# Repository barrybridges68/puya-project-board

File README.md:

# puya-project-board
Multi purpose PUYA py32 project board

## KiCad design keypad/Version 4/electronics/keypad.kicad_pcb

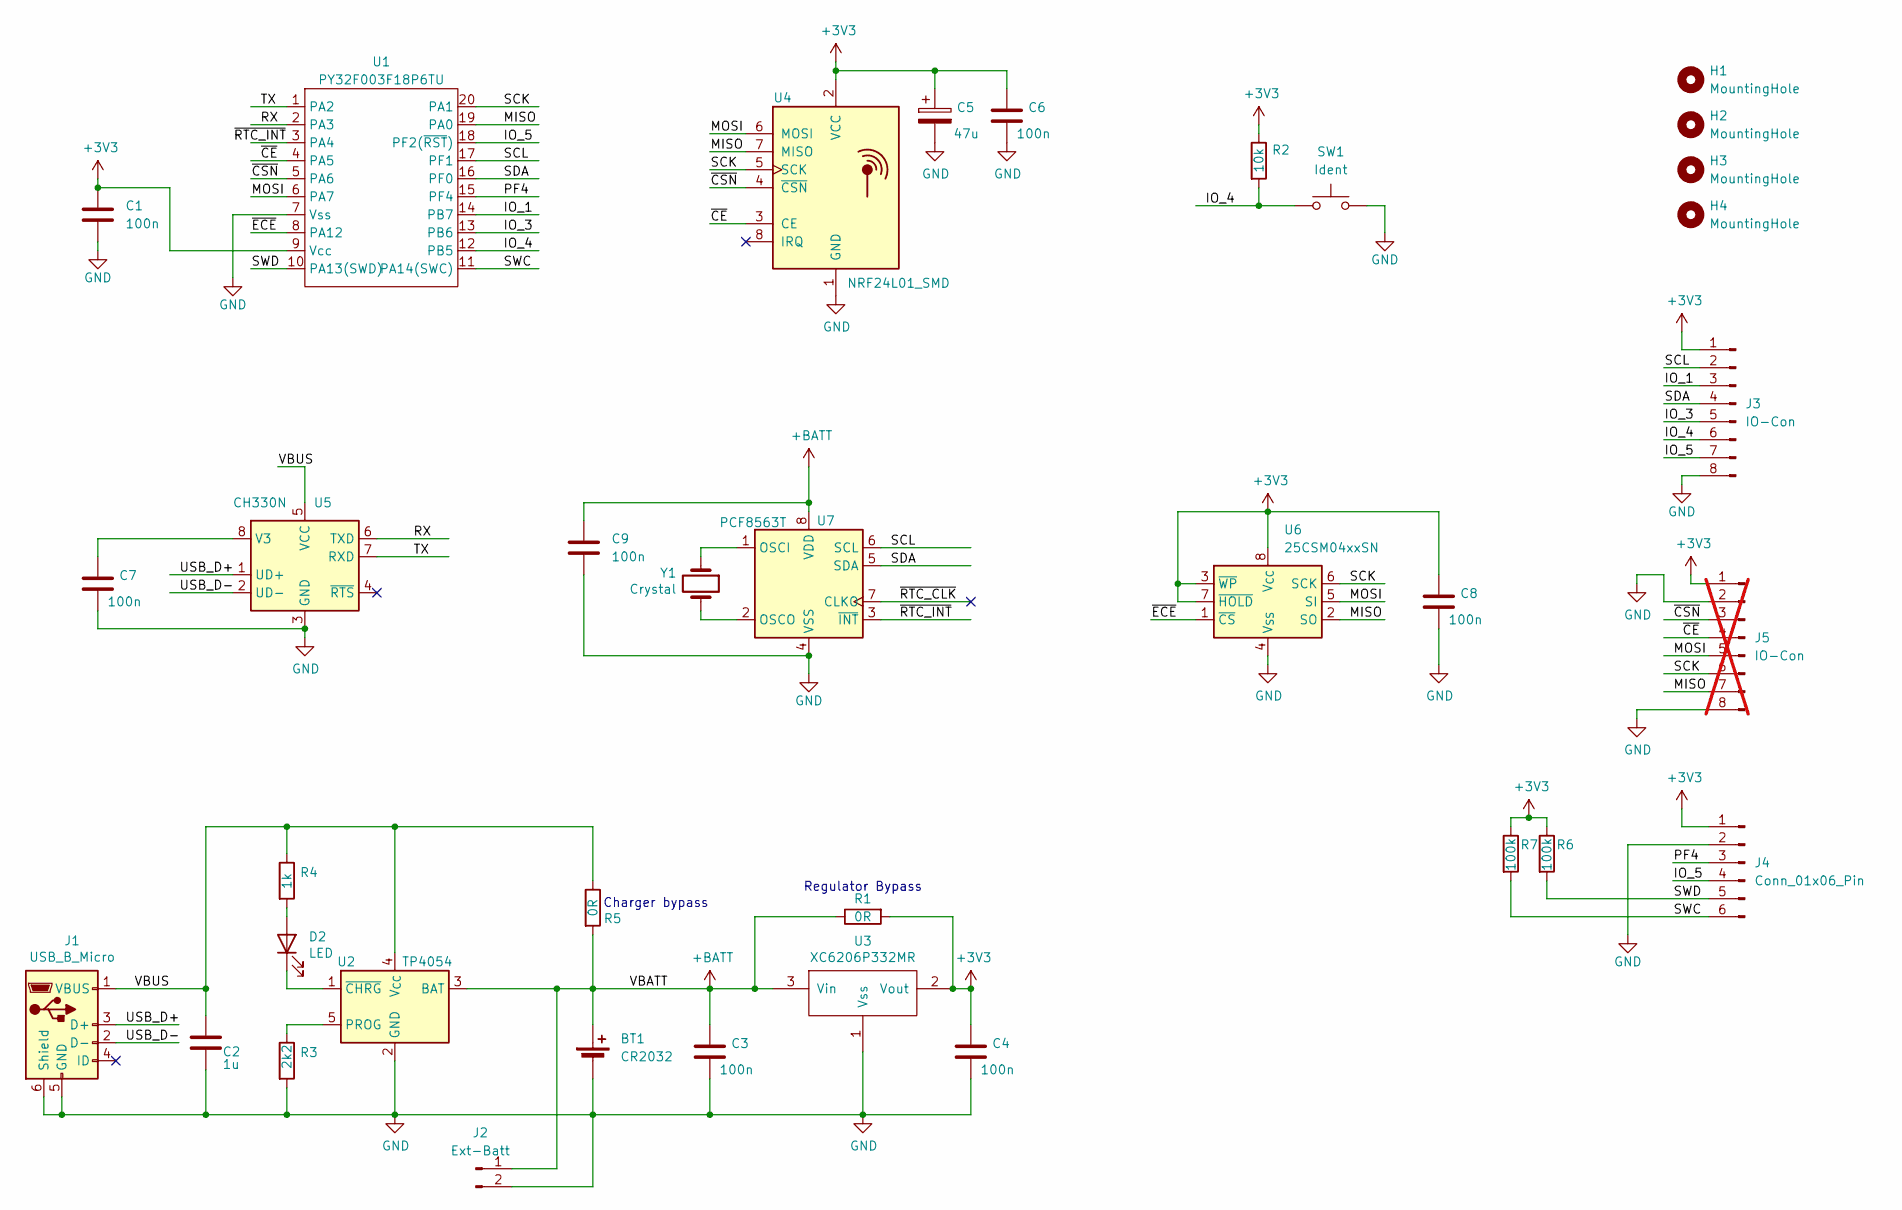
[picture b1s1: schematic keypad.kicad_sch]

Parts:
BT1: CR2032; BatteryHolder_Renata_SMTU2032-LF_1x2032
C1, C3, C4, C6, C7, C8, C9: 100n; C_0603_1608Metric_Pad1.08x0.95mm_HandSolder
C2: 1u; C_0603_1608Metric_Pad1.08x0.95mm_HandSolder
C5: 47u; C_1206_3216Metric_Pad1.33x1.80mm_HandSolder
D2: LED; LED_0603_1608Metric_Pad1.05x0.95mm_HandSolder
H1, H2, H3, H4: MountingHole; MountingHole_2.2mm_M2
J1: USB_B_Micro; USB_Micro-B_Molex-105017-0001
J2: Ext-Batt; PinHeader_1x02_P2.54mm_Vertical
J3: IO-Con; PinHeader_2x04_P2.54mm_Vertical
J4: Conn_01x06_Pin; PinHeader_2x03_P2.54mm_Vertical
J5: IO-Con; PinHeader_2x04_P2.54mm_Vertical; not fitted
R1, R5: 0R; R_0603_1608Metric_Pad0.98x0.95mm_HandSolder
R2: 10k; R_0603_1608Metric_Pad0.98x0.95mm_HandSolder
R3: 2k2; R_0603_1608Metric_Pad0.98x0.95mm_HandSolder
R4: 1k; R_0603_1608Metric_Pad0.98x0.95mm_HandSolder
R6, R7: 100k; R_0603_1608Metric_Pad0.98x0.95mm_HandSolder
SW1: Ident; 4.50x4.50-tactile
U1: PY32F003F18P6TU; TSSOP-20_4.4x6.5mm_P0.65mm
U2: TP4054; SOT-23-5
U3: XC6206P332MR; SOT-23
U4: NRF24L01_SMD; NRF24L01-SMD
U5: CH330N; SOIC-8_3.9x4.9mm_P1.27mm
U6: 25CSM04xxSN; SOIC-8W_5.3x5.3mm_P1.27mm
U7: PCF8563T; SOIC-8_3.9x4.9mm_P1.27mm
Y1: Crystal; Crystal_C38-LF_D3.0mm_L8.0mm_Horizontal

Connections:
+3V3: C1.1, C4.1, C5.1, C6.1, C8.1, J3.1, J4.1, J5.1, R1.2, R2.1, R6.1, R7.1, U1.9 (Vcc), U3.2 (Vout), U4.2 (VCC), U6.3 (~WP), U6.7 (~HOLD), U6.8 (V_{CC})
+BATT: BT1.1 (+), C3.1, C9.1, J2.1, R1.1, R5.2, U2.3 (BAT), U3.3 (Vin), U7.8 (VDD)
/IO_1: J3.3, U1.14 (PB7)
/IO_3: J3.5, U1.13 (PB6)
/IO_4: J3.6, R2.2, SW1.1, U1.12 (PB5)
/IO_5: J3.7, J4.4, U1.18 (PF2(~RST))
/MISO: J5.7, U1.19 (PA0), U4.7 (MISO), U6.2 (SO)
/MOSI: J5.5, U1.6 (PA7), U4.6 (MOSI), U6.5 (SI)
/PF4: J4.3, U1.15 (PF4)
/RX: U1.2 (PA3), U5.6 (TXD)
/SCK: J5.6, U1.20 (PA1), U4.5 (SCK), U6.6 (SCK)
/SCL: J3.2, U1.17 (PF1), U7.6 (SCL)
/SDA: J3.4, U1.16 (PF0), U7.5 (SDA)
/SWC: J4.6, R7.2, U1.11 (PA14(SWC))
/SWD: J4.5, R6.2, U1.10 (PA13(SWD))
/TX: U1.1 (PA2), U5.7 (RXD)
/USB_D+: J1.3 (D+), U5.1 (UD+)
/USB_D-: J1.2 (D-), U5.2 (UD-)
/VBUS: C2.1, J1.1 (VBUS), R4.1, R5.1, U2.4 (V_{CC}), U5.5 (VCC)
/~CE: J5.4, U1.4 (PA5), U4.3 (CE)
/~CSN: J5.3, U1.5 (PA6), U4.4 (~CSN)
/~ECE: U1.8 (PA12), U6.1 (~CS)
/~RTC_CLK: U7.7 (CLKO)
/~RTC_INT: U1.3 (PA4), U7.3 (~INT)
GND: BT1.2 (-), C1.2, C2.2, C3.2, C4.2, C5.2, C6.2, C7.2, C8.2, C9.2, J1.5 (GND), J1.6 (Shield), J2.2, J3.8, J4.2, J5.2, J5.8, R3.2, SW1.2, U1.7 (Vss), U2.2 (GND), U3.1 (Vss), U4.1 (GND), U5.3 (GND), U6.4 (V_{SS}), U7.4 (VSS)
unnamed: D2.2 (A), R4.2
unnamed: D2.1 (K), U2.1 (~CHRG)
unnamed: R3.1, U2.5 (PROG)
unnamed: C7.1, U5.8 (V3)
unnamed: U7.1 (OSCI), Y1.1
unnamed: U7.2 (OSCO), Y1.2

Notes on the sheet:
Regulator Bypass
Charger bypass

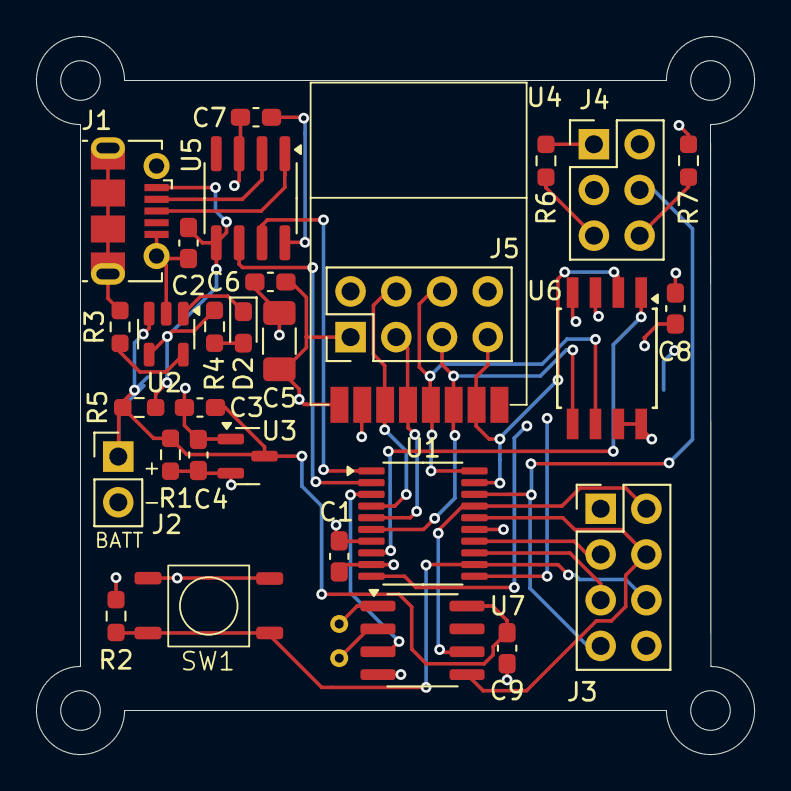
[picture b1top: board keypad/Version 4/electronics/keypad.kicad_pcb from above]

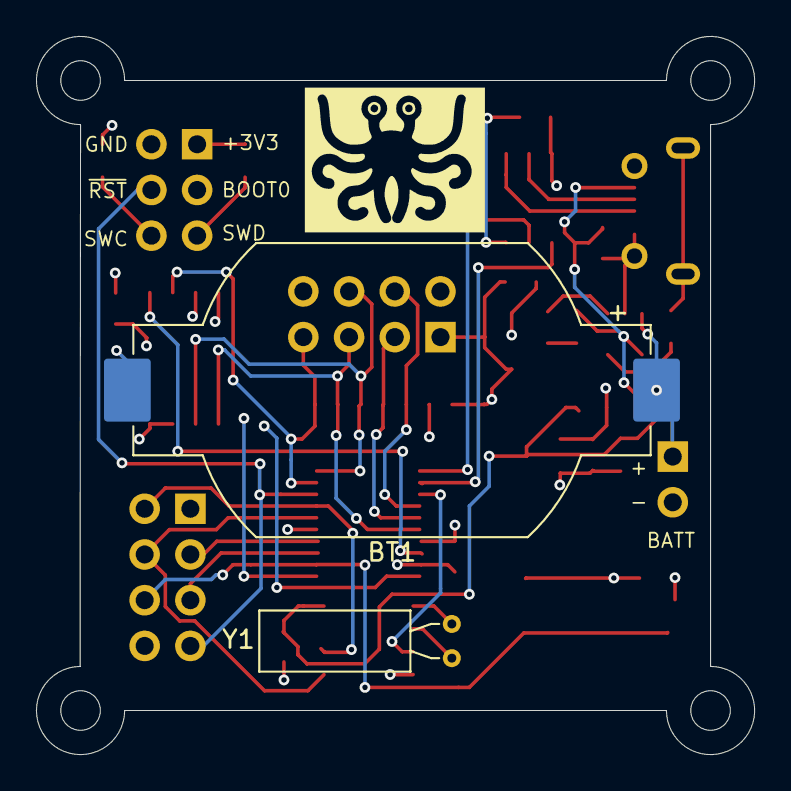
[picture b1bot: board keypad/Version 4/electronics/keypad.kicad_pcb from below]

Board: 4 copper layers, 39.9 x 39.9 mm, 36 parts (2 on the bottom side), 30 nets.

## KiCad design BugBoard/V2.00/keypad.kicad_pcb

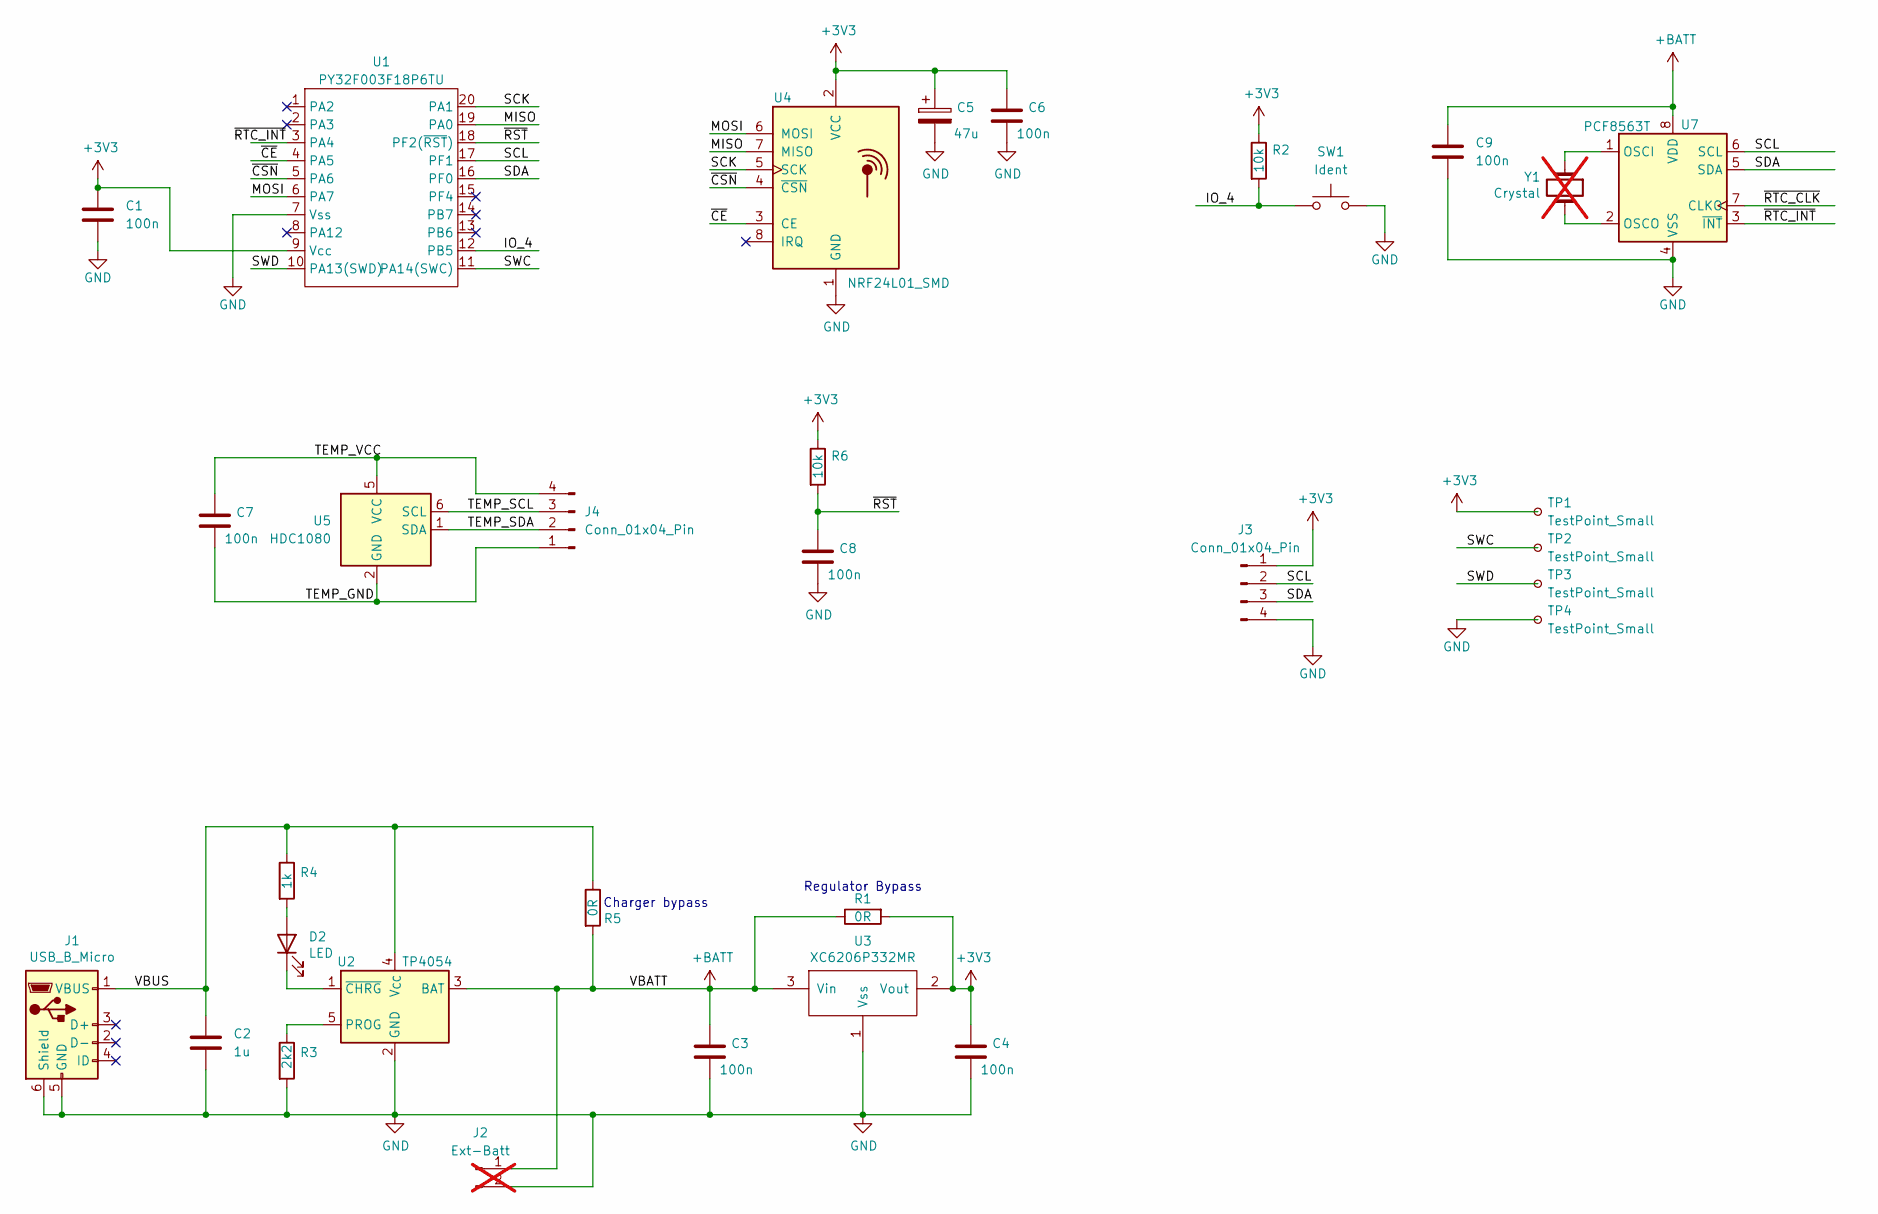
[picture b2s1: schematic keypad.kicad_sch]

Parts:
C1, C3, C4, C6, C7, C8, C9: 100n; C_0603_1608Metric_Pad1.08x0.95mm_HandSolder
C2: 1u; C_0603_1608Metric_Pad1.08x0.95mm_HandSolder
C5: 47u; C_1206_3216Metric_Pad1.33x1.80mm_HandSolder
D2: LED; LED_0603_1608Metric_Pad1.05x0.95mm_HandSolder
J1: USB_B_Micro; USB_Micro-B_Molex-105017-0001
J2: Ext-Batt; PinHeader_1x02_P2.54mm_Vertical; not fitted
J3, J4: Conn_01x04_Pin; JST_GH_SM04B-GHS-TB_1x04-1MP_P1.25mm_Horizontal
R1, R5: 0R; R_0603_1608Metric_Pad0.98x0.95mm_HandSolder
R2, R6: 10k; R_0603_1608Metric_Pad0.98x0.95mm_HandSolder
R3: 2k2; R_0603_1608Metric_Pad0.98x0.95mm_HandSolder
R4: 1k; R_0603_1608Metric_Pad0.98x0.95mm_HandSolder
SW1: Ident; 4.50x4.50-tactile
TP1, TP2, TP3, TP4: TestPoint_Small; TestPoint_Pad_1.0x1.0mm
U1: PY32F003F18P6TU; TSSOP-20_4.4x6.5mm_P0.65mm
U2: TP4054; SOT-23-5
U3: XC6206P332MR; SOT-23
U4: NRF24L01_SMD; NRF24L01-SMD
U5: HDC1080; Texas_PWSON-N6
U7: PCF8563T; SOIC-8_3.9x4.9mm_P1.27mm
Y1: Crystal; Crystal_C38-LF_D3.0mm_L8.0mm_Horizontal; not fitted

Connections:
+3V3: C1.1, C4.1, C5.1, C6.1, J3.1, R1.2, R2.1, R6.1, TP1.1, U1.9 (Vcc), U3.2 (Vout), U4.2 (VCC)
+BATT: C3.1, C9.1, J2.1, R1.1, R5.2, U2.3 (BAT), U3.3 (Vin), U7.8 (VDD)
/IO_4: R2.2, SW1.1, U1.12 (PB5)
/MISO: U1.19 (PA0), U4.7 (MISO)
/MOSI: U1.6 (PA7), U4.6 (MOSI)
/SCK: U1.20 (PA1), U4.5 (SCK)
/SCL: J3.2, U1.17 (PF1), U7.6 (SCL)
/SDA: J3.3, U1.16 (PF0), U7.5 (SDA)
/SWC: TP2.1, U1.11 (PA14(SWC))
/SWD: TP3.1, U1.10 (PA13(SWD))
/TEMP_GND: C7.2, J4.1, U5.2 (GND)
/TEMP_SCL: J4.3, U5.6 (SCL)
/TEMP_SDA: J4.2, U5.1 (SDA)
/TEMP_VCC: C7.1, J4.4, U5.5 (VCC)
/VBUS: C2.1, J1.1 (VBUS), R4.1, R5.1, U2.4 (V_{CC})
/~CE: U1.4 (PA5), U4.3 (CE)
/~CSN: U1.5 (PA6), U4.4 (~CSN)
/~RST: C8.1, R6.2, U1.18 (PF2(~RST))
/~RTC_CLK: U7.7 (CLKO)
/~RTC_INT: U1.3 (PA4), U7.3 (~INT)
GND: C1.2, C2.2, C3.2, C4.2, C5.2, C6.2, C8.2, C9.2, J1.5 (GND), J1.6 (Shield), J2.2, J3.4, R3.2, SW1.2, TP4.1, U1.7 (Vss), U2.2 (GND), U3.1 (Vss), U4.1 (GND), U7.4 (VSS)
unnamed: D2.2 (A), R4.2
unnamed: D2.1 (K), U2.1 (~CHRG)
unnamed: R3.1, U2.5 (PROG)
unnamed: U7.1 (OSCI), Y1.1
unnamed: U7.2 (OSCO), Y1.2

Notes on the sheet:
Regulator Bypass
Charger bypass

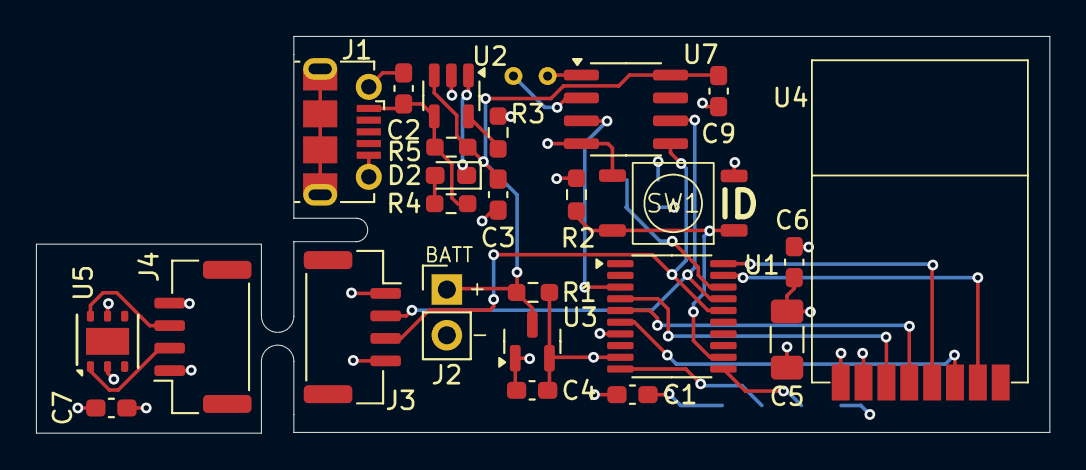
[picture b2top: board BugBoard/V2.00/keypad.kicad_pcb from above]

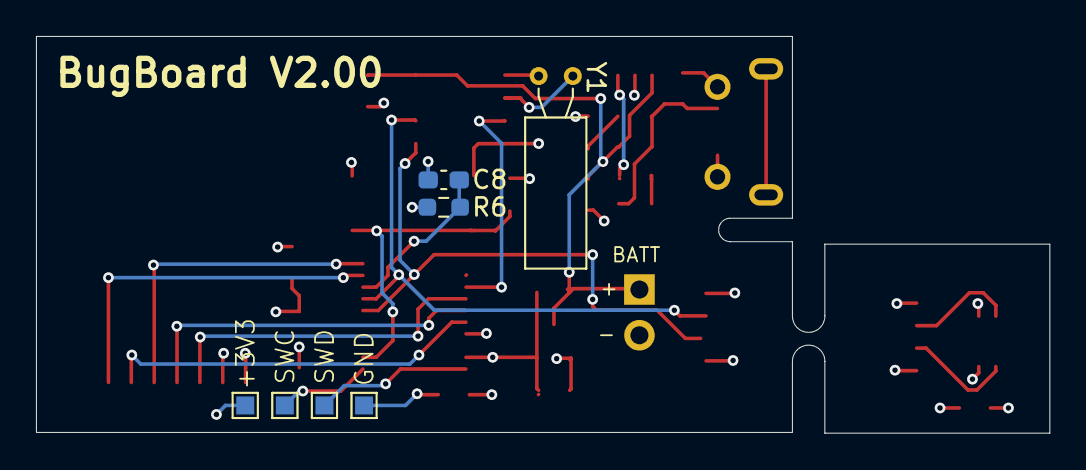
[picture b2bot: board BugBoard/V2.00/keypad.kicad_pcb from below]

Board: 4 copper layers, 56.3 x 22.0 mm, 32 parts (7 on the bottom side), 25 nets.

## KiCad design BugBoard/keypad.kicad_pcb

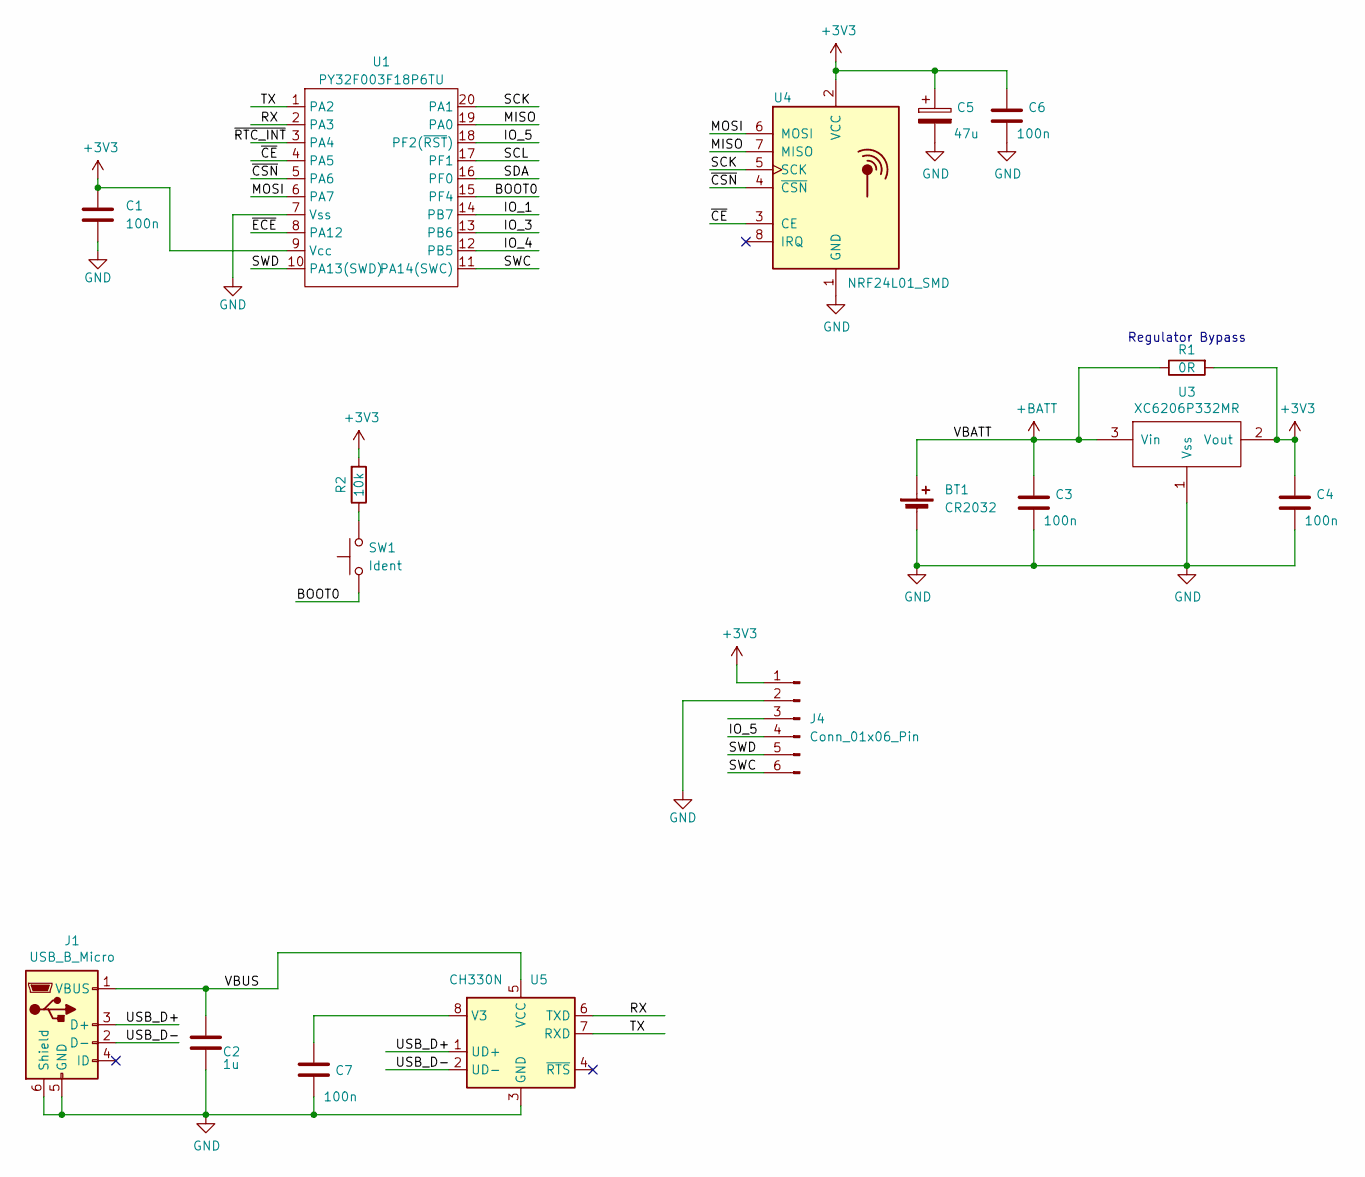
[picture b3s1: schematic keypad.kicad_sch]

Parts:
BT1: CR2032; BatteryHolder_Renata_SMTU2032-LF_1x2032
C1, C3, C4, C6, C7: 100n; C_0603_1608Metric_Pad1.08x0.95mm_HandSolder
C2: 1u; C_0603_1608Metric_Pad1.08x0.95mm_HandSolder
C5: 47u; C_1206_3216Metric_Pad1.33x1.80mm_HandSolder
J1: USB_B_Micro; USB_Micro-B_Molex-105017-0001
J4: Conn_01x06_Pin; PinHeader_2x03_P2.54mm_Vertical
R1: 0R; R_0603_1608Metric_Pad0.98x0.95mm_HandSolder
R2: 10k; R_0603_1608Metric_Pad0.98x0.95mm_HandSolder
SW1: Ident; 4.50x4.50-tactile
U1: PY32F003F18P6TU; TSSOP-20_4.4x6.5mm_P0.65mm
U3: XC6206P332MR; SOT-23
U4: NRF24L01_SMD; NRF24L01-SMD
U5: CH330N; SOIC-8_3.9x4.9mm_P1.27mm

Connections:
+3V3: C1.1, C4.1, C5.1, C6.1, J4.1, R1.2, R2.2, U1.9 (Vcc), U3.2 (Vout), U4.2 (VCC)
+BATT: BT1.1 (+), C3.1, R1.1, U3.3 (Vin)
/BOOT0: SW1.1, U1.15 (PF4); also elsewhere on the board
/IO_1: U1.14 (PB7)
/IO_3: U1.13 (PB6)
/IO_4: U1.12 (PB5)
/IO_5: J4.4, U1.18 (PF2(~RST))
/MISO: U1.19 (PA0), U4.7 (MISO)
/MOSI: U1.6 (PA7), U4.6 (MOSI)
/RX: U1.2 (PA3), U5.6 (TXD)
/SCK: U1.20 (PA1), U4.5 (SCK)
/SCL: U1.17 (PF1)
/SDA: U1.16 (PF0)
/SWC: J4.6, U1.11 (PA14(SWC))
/SWD: J4.5, U1.10 (PA13(SWD))
/TX: U1.1 (PA2), U5.7 (RXD)
/USB_D+: J1.3 (D+), U5.1 (UD+)
/USB_D-: J1.2 (D-), U5.2 (UD-)
/VBUS: C2.1, J1.1 (VBUS), U5.5 (VCC)
/~CE: U1.4 (PA5), U4.3 (CE)
/~CSN: U1.5 (PA6), U4.4 (~CSN)
/~ECE: U1.8 (PA12)
/~RTC_INT: U1.3 (PA4)
GND: BT1.2 (-), C1.2, C2.2, C3.2, C4.2, C5.2, C6.2, C7.2, J1.5 (GND), J1.6 (Shield), J4.2, U1.7 (Vss), U3.1 (Vss), U4.1 (GND), U5.3 (GND)
unnamed 24: R2.1, SW1.2; also elsewhere on the board
unnamed: C7.1, U5.8 (V3)

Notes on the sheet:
Regulator Bypass

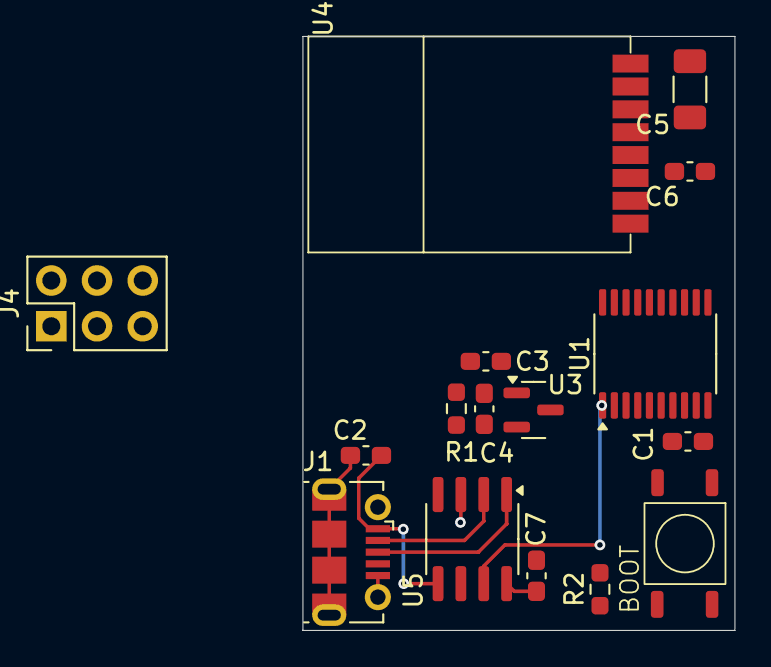
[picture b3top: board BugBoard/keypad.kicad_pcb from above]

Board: 4 copper layers, 24.0 x 33.0 mm, 17 parts (1 on the bottom side), 19 nets.

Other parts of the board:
BOOT: Ident; 4.50x4.50-tactile

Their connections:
/BOOT0: BOOT.1; also elsewhere on the board
unnamed 24: BOOT.2; also elsewhere on the board

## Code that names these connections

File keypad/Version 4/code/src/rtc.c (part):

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rtc_date_time_t rtc_date_time;
#define PCF8563T_MASTER_ADDRESS 0xA2

#define RTC_INT_PORT  GPIOA
#define RTC_INT_PIN   LL_GPIO_PIN_4

/**
 * @brief Basic definitions
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
	__HAL_RCC_GPIOA_CLK_ENABLE();
    
    /* PA4 as input */
    GPIO_InitStruct.Pin = LL_GPIO_PIN_4;
    GPIO_InitStruct.Mode = LL_GPIO_MODE_INPUT;
    GPIO_InitStruct.Pull = LL_GPIO_PULL_UP;
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    EXTI_InitStruct.Trigger = LL_EXTI_TRIGGER_FALLING;
    LL_EXTI_Init(&EXTI_InitStruct);

    // PF1 SCL
    GPIO_InitStruct.Pin = LL_GPIO_PIN_1;
    GPIO_InitStruct.Mode = LL_GPIO_MODE_ALTERNATE;
    GPIO_InitStruct.Speed = LL_GPIO_SPEED_FREQ_HIGH;
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    GPIO_InitStruct.Alternate = LL_GPIO_AF_12;
    LL_GPIO_Init(GPIOF, &GPIO_InitStruct);

    // PF0 SDA
    GPIO_InitStruct.Pin = LL_GPIO_PIN_0;
    GPIO_InitStruct.Alternate = LL_GPIO_AF_12;
    LL_GPIO_Init(GPIOF, &GPIO_InitStruct);
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
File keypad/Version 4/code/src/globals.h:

#ifndef GLOBALS_H
#define GLOBALS_H

// Your global variables and function declarations go here

#define IO_4 GPIO_IDR_ID5
#define IO_3 GPIO_IDR_ID6
#define IO_1 GPIO_IDR_ID7

#endif // GLOBALS_H

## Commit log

2025-01-16 Added bugboard
2025-01-16 PCB update
2025-01-16 Added JST i2c connector
2025-01-27 Finished code. Added bug board
2025-02-08 Various changes and updates to bugboard
2025-02-09 Flash code added and littlefs
2025-02-16 Added basic interpreter (untested) now adding forth
